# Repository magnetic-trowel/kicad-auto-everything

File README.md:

# kicad-auto-everything
helper systems for LLMing KiCad

## Research

- [`docs/INDEX.md`](docs/INDEX.md): start here. Short digests link to small
  focused topic docs on placement and routing algorithms, LLMs for EDA, KiCad
  integration, layout rules, verification, benchmarks, and licensing.
- [`research_notes/LLM driven PCB placement and routing/`](research_notes/LLM%20driven%20PCB%20placement%20and%20routing/):
  the raw survey notes the docs cite as evidence.

## Design synthesis

- [`synth/`](synth/README.md) (`kaesynth`): an LLM writes a typed circuit description
  (`designs/<slug>/design.py`); `kaesynth build` checks it (ratings vs worst-case net voltage,
  isolation domains, protection, provenance), writes a KiCad 10 schematic and project, proves the
  schematic's netlist matches, and emits placement intent for the placer/router.
- [`designs/`](designs/): worked examples from plain-language briefs.

## License

Code is [GPL-3.0-or-later](LICENSE); documentation and research notes are
CC-BY-4.0, rule packs CC0-1.0, datasets CDLA-Permissive-2.0, and model weights
Apache-2.0. See [`LICENSING.md`](LICENSING.md) for details and
[`CONTRIBUTING.md`](CONTRIBUTING.md) for how to contribute (DCO sign-off).

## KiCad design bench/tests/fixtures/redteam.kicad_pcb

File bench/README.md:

# kaebench

Benchmark harness for automated and LLM-driven KiCad placement and routing. It
fetches real boards from a manifest, turns them into route and place tasks, runs a
method (an "adapter") on each task k times, and scores every attempt by re-opening
the saved board with `kicad-cli` under the board's own rules. Design rationale:
[docs/topics/verification/harness.md](../docs/topics/verification/harness.md).

## Setup (Ubuntu 22.04/24.04)

```bash
git clone https://github.com/magnetic-trowel/kicad-auto-everything
cd kicad-auto-everything
bench/scripts/setup.sh          # KiCad 10 (PPA, no recommends), bench/.venv (and upstream Freerouting 2.5.0, explicit use only)
tools/research/routing/install_freerouting_fork.sh <ref> --pin   # the Freerouting fork, pinned: the control
source bench/.venv/bin/activate
kaebench doctor
```

**Without sudo** the same script still works:
- KiCad runs from the official `kicad/kicad:10.0.7` image, unpacked into `~/.cache/kaebench` (~2.5 GB). It needs no root and no `/dev/fuse`.
- It uses an installed Apptainer or Singularity. Without one, it installs Apptainer 1.5.4 rootless into `~/.cache/kaebench/apptainer` (~160 MB) with Apptainer's own `install-unprivileged.sh`, which unpacks EL8 RPMs. Python stand-ins replace `rpm2cpio` and `cpio` if they are missing.
- The rootless install needs x86_64 and unprivileged user namespaces. Check with `unshare -Ur true && echo ok`. Ubuntu 22.04 allows them by default; 24.04 blocks them unless an admin relaxes `kernel.apparmor_restrict_unprivileged_userns`.
- If `python3-venv` is missing, the venv comes from `uv`.
- Freerouting, the venv and `env.sh` all live in your home directory. Set `KAE_HOME` to put the large files on another disk.
- `source bench/.venv/bin/activate` picks up the KiCad wrapper. Force this route with `--kicad container`.
- The container sees `$HOME`, `/tmp` and the current directory. For a `--workdir` elsewhere, export `APPTAINER_BIND=/that/path`.

Other OSes or setups: point `KAE_KICAD_CLI` / `KAE_KICAD_PYTHON` at KiCad 10. Both accept a command with a wrapper, e.g. `flatpak run --command=kicad-cli org.kicad.KiCad`, or use `KAE_KICAD_WRAP` as a prefix for both. The container set-up points `KAE_KICAD_WRAP` at `kicad-exec`, which shows KiCad only the CPUs a job may use (`KAE_KICAD_THREADS`, else the queue's `KAEQ_CPUS`, else `nproc`; `KAE_KICAD_THREADS=0` turns the cap off): KiCad otherwise starts one thread per CPU on the machine. The Python must be able to `import pcbnew`. Freerouting is the build named by `KAE_FREEROUTING` (a binary or JAR; the JAR needs Java 25), else the one pinned in `$KAE_HOME/kae-freerouting.pin` (the magnetic-trowel fork, the same pin the bridge uses); with neither, runs stop with an error. Nothing picks the newest install. Run `pytest bench/tests` to check the install.

## Usage

```bash
M=bench/manifests/candidates.jsonl
kaebench fetch   -m $M -j 8                 # download boards at pinned commits (verifies sha256)
kaebench prepare -m $M -j 8                 # convert to KiCad 10, qualify, build route/place tasks
kaebench run --adapter reference --kinds route,place --probe freerouting -j 8 --name human
kaebench run --adapter freerouting -k 1 --timeout 900 -j 8 --name fr-fork      # the pinned fork; deterministic: one attempt
kaebench report kae-work/results/human kae-work/results/fr-fork
```

Everything lives under `--workdir` (default `./kae-work`): `cache/` (fetched files),
`tasks/<id>/{reference,route,place,place-fixed}/` and `results/<run>/<adapter>/<kind>/<id>/attempt-N/`.
Runs resume: re-running with the same `--name` skips finished attempts.

Useful filters on `fetch`/`prepare`: `--tiers permissive`, `--tags rf,ddr`, `--only id1,id2`,
`--limit N`. On `run`: `--splits A,B` (A ≤ 31 pads, B ≤ 100, C larger), `--all` to include
boards whose human layout is not clean.

## Suites

`bench/suites/*.txt` are board-id lists for `--only @FILE`:
- `kaebench tasks --write-suite FILE` writes the boards that qualified on your KiCad version.
- `qualified-kicad-10.0.7.txt`: the 112 manifest boards that qualified on KiCad 10.0.7.
- `pcbworld-d3{a,b,c}-test.txt` are PCBWorld's D3 eval splits (99 / 10 / 10).

### Reproducing PCBWorld's routing baseline

PCBWorld's D3 boards are PCBench boards run through PCBWorld's own chain: KiCad 5→9.0.8 conversion, DRC repair, guide generation. Build them with that chain, then import them:

```bash
# in a PCBWorld checkout (https://github.com/LGAI-Research/PCBWorld); builds its KiCad engine
export PCBWORLD_DATA_ROOT=$PWD/var/datasets
bash tools/quickstart/prepare_pcbench.sh --workers 16
# back in this repo
kaebench --workdir kae-d3 prepare-dir --dir $PCBWORLD_DATA_ROOT/pcbench/exacad_sorted \
  --board-glob processed_v9_guide_v3.kicad_pcb --only @bench/suites/pcbworld-d3a-test.txt --kinds route -j 16
KAE_FREEROUTING=<a Freerouting release> kaebench --workdir kae-d3 run --adapter freerouting --passes 10 -k 5 -j 16 --name fr-release-mp10
```

PCBWorld published Freerouting 2.1.0 `-mp 10` at 0.80 (D3-A) and 0.78 (D3-B) clean-pass @5. Our scoring re-saves boards with KiCad 10 and uses each board's own severities. Expect close but not identical numbers; report both.

## Adapters

| Adapter | What it does |
|---|---|
| `reference` | The human layout: original copper (route) or original placement (place) |
| `noop` | Returns the task input unchanged (lower bound) |
| `freerouting` | Specctra DSN → the pinned Freerouting (the fork, our control; `-mt 1`, analytics off, per-attempt pass schedule, neck-down off, board edge/hole clearances passed, DSN widths clamped to the board minimum) → SES with placement block stripped → import |
| `freerouting-stock` | Same round trip with Freerouting's default settings; for explicit, deliberate use only (stock 2.5.0 is no longer a control) |
| any name + `--command` | External tool; template placeholders `{input} {output} {workdir} {kind} {attempt} {timeout}` |

Example external router: `kaebench run --adapter myrouter --command "python my_router.py {input} {output}"`.
The tool reads `{input}` (a `.kicad_pcb` with its project files beside it) and writes `{output}`.

**Sandbox.** `--command` methods run under bubblewrap (`bwrap`):
- no network;
- a private `/tmp` and `/var/tmp`;
- a home directory that shows only the kaebench tool cache (`KAE_HOME`), the current directory and any `--sandbox-ro PATH`;
- the workdir's tasks and results hidden, plus anything in `KAE_SANDBOX_HIDE` (colon-separated);
- only the attempt's own work directory writable.

A method can't read the human layout it is scored against, download it, or touch other attempts. On timeout the whole sandbox is killed. `--sandbox-net` allows network access, for LLM methods. `--no-sandbox` turns the sandbox off; the report then marks those attempts as unsandboxed.

## Scoring

- **Rebuilt board, reference rules, fresh process.** The scorer never judges the file a method wrote. It rebuilds the board from the task input plus only the changes the task allows:
  - route: the tracks, arcs and vias, copied as KiCad's own re-save of them, plus (score v10) the copper zones the method adds, unfilled, and each pad's own zone connection (`zone_connect`);
  - place: each unlocked footprint's position, rotation and side.

  The rebuilt board gets the reference `.kicad_pro`/`.kicad_dru`, zones are refilled, and `kicad-cli pcb drc` runs. Edits to rules, outline, keepouts, the task's zones, other pad properties, layers or nets can't change a score. Rules files a method writes are never read: the output is opened next to the task's own project files.
  - Teardrops, groups and tuning patterns are part of the routing. They are stripped from task inputs and are not transplanted or scored.
- **Integrity (`valid`).** Anything else the method changed is still detected, by comparing KiCad re-saves of output and input with the allowed changes normalized away (`foreign` lists them). Such a result is invalid.
  - Route results must keep placement, pad nets and every other board object, and route only on the board's copper layers and nets.
  - **Added zones** (route, joint and joint-fixed tasks, score v10). A method may pour copper. Each added zone must be a copper zone (no rule area or keepout) on the board's enabled copper layers, on a net the task has (no new nets, no net-less zones), inside the board's outer outline (10 µm slack for arcs), clear of rule areas that forbid pours on its layers, at a priority different from every zone it overlaps on a shared layer (KiCad 10.0.7's filler deadlocks on overlapping zones of different nets tied on priority and uuid), and with a unique uuid. Violations make the result invalid (`integrity.zones`, reasons in `zone_problems`). The task's own zones must stay exactly as given. These checks look at zone outlines; DRC checks the refilled copper (clearances, edge clearance, `items_not_allowed` in keepouts). Fills a method writes are ignored: DRC refills every zone, and the uncapped unconnected count fills them too, at start and end alike. Give new zones explicit pad-connection settings (clearance, thermal gap, spoke width) rather than relying on board defaults. No count or area cap; refilling many zones counts against `KAE_DRC_TIMEOUT` like anything else. In joint tasks the placement half ignores added zones and pads' zone connection (placement legality is judged on the placement alone); the routing half transplants and checks them onto that placement as in a route task.
  - Place results must keep pad nets and every non-pose property, leave anchored footprints where they are (locked ones, and ones carrying Edge.Cuts, which are part of the board outline), and not add or remove footprints or copper.
- **Copy check.** `copy` reports how much of the output reproduces the human layout exactly: tracks to 1 µm, or poses to 1 µm and 0.01°; and `copy.zones`, added zones whose outline overlaps a human zone on the same net and a shared layer with IoU ≥ 0.8. `suspect_copy` flags at least 20 tracks and 60% matching, at least 5 parts and 50%, or any copied zone. It is report-only until calibrated on real methods. The sandbox is the enforcement.
- **Route metrics.**
  - `clean`: valid, 0 unconnected, 0 error-level DRC violations. Severities come from the board's own project; library-environment checks are excluded.
  - `completion`: share of start-of-task unconnected items now routed.
  - `wl_ratio`: track length relative to the human layout.
  - `via_delta`: via count minus the human layout's.
- **Place metrics.**
  - `legal`: valid, no courtyard, clearance, edge-clearance, hole or keepout errors, and no footprint with more pad centres outside the board outline than the same footprint has in the human placement. Edge connectors may overhang as far as the designer's do.
  - `hpwl_ratio` relative to the human placement.
  - With `--probe freerouting`, the rebuilt placement is routed by a fixed router and scored like a route result, Cypress-style. An external router can be the probe: `--probe NAME --probe-command TEMPLATE` (or `probe=NAME,probe_command=TEMPLATE` in an `--arm`, without commas), run sandboxed as a route method.
- **Joint metrics** (`--kinds joint`: place and route in one output, from the place task's input).
  - The output's footprint poses are rebuilt into the place input. Placement integrity and `legal` are judged on that placement alone.
  - Its tracks and vias are then rebuilt onto that placement and scored like a route result.
  - Valid only if both parts are; `clean` also requires `legal`.
  - Baselines: `reference` (the human layout) and `human-freerouting` (Freerouting on the human placement).
- **Place-fixed tasks** (`--kinds place-fixed`, and `joint-fixed` for place and route from its input). A place task frees every unlocked footprint, the connectors and mounting holes too, so a placer can beat the human on wire length with a board that no longer fits its enclosure or cables. Place-fixed keeps the board's mechanical interface at the human pose, locked in the input, so it is scored exactly like a locked footprint (`locked_moved`); everything else is placed. Scoring and baselines are those of `place` and `joint`.
  - Fixed: connectors (USB, pin headers and sockets, JST/Molex/FPC/FFC, terminal blocks, barrel and audio jacks, RF, SD/SIM and card-edge slots, wire pads); mounting (screw holes, standoffs, fiducials, all-NPTH footprints); user-facing parts (switches, keyboard key switches such as Cherry MX, Kailh/Choc and Gateron, buttons, panel pots and encoders, displays, through-hole, light-pipe and LED-bar indicators, buzzers and speakers).
  - Free (the user's choices on borderline parts): programming and debug headers (JTAG, SWD, ISP/ICSP, PDI/UPDI, Tag-Connect, debug or prog in the name, value, description or reference, or a small header whose signal nets are one such interface), SMD LEDs, test points, jumpers and solder bridges (also pin headers with a jumper value), batteries and battery holders, trimmers, IC sockets; also net ties, heatsinks and plug-in modules. UART and display headers stay fixed.
  - The rules follow the placement research classifier (`kae.place.fixed`); on the 112 qualified boards the two fix the same parts on 99 boards.
  - Rules, first match wins (`kicad_scripts/mech_rules.py` documents each, `rules_version` is recorded): exclusions; KiCad library (`Connector*`, `TerminalBlock*`, `MountingHole*`, `Fiducial*`, `Button_Switch*`, `Potentiometer*`, `Rotary_Encoder*`, `Display*`, `Buzzer_Beeper*`, `LED_THT`, connector makers); all pads NPTH; a THT LED name; a passive/diode/IC library, package name or reference (R, C, D, Q, ...) stops the rest; footprint-name patterns; KiCad symbol names as values (`Conn_01x04`, `SW_Push`); reference prefixes (J, P, H, MH, FID, SW, RV, ...) when the footprint fits. A connector that is a programming or debug header is then freed.
  - The task record lists every fixed part with its class and rule (`tasks["place-fixed"].fixed_mech`) and `movable`. `prepare --fixed-overrides FILE` takes `{"<board id>": {"fix": [refs], "free": [refs]}}` and records what it applied. Designer-locked parts and parts carrying Edge.Cuts stay anchored either way.
  - The human placement must also pass the place-fixed round trip. A board that fails it keeps its other tasks; runs skip only its place-fixed and joint-fixed tasks.
- **Degenerate place tasks.** Each place task records `movable`, the number of footprints a placer may move. A board whose parts are nearly all locked is trivially legal. `run --min-movable N` skips place, joint, place-fixed and joint-fixed tasks with fewer than N movable footprints (default 0: none are skipped).
- **Best-of-k** picks the attempt by clean, then completion, errors, track length (PCBWorld's best-potential @k). The report shows `cp1` (attempt 0) and `cpk`.
- **Rescoring.** After a scoring fix, `kaebench rescore RUN_DIR -j N` scores a run's saved outputs (and saved probe routes) again with the current scorer, without re-running the method. Each attempt records the version it was rescored from.
- **Versions.** Every attempt records `score_version` (now 10; v10 lets route and joint methods add zones and set pads' zone connection, and scores outputs without either exactly as v9). Tasks need task spec 5: locked footprints and footprints carrying Edge.Cuts stay in place, teardrops are stripped, repeated footprint uuids are made unique, and the human layout must pass the round trip. Place-fixed and joint-fixed need task spec 8 (classifier rules 4). From task spec 11 every task is limited to the copper layers the board uses (`kicad_scripts/layer_plan.py`); tasks of older specs must be prepared again. Re-run `prepare --force` on older task folders.
- **Red-team tests.** `bench/tests/test_redteam.py` runs cheating methods (move parts, delete a keepout, grow the outline, add a layer, shrink pads, swap nets, ship own rules, read or overwrite the reference, use the network) and requires each to be invalid, blocked or ineffective. Add a case for every new cheat found.

## Manifests

`bench/manifests/*.jsonl`, one board per line: `id`, `repo`, `commit` (40-hex),
`pcb_path`, `license` (required), plus `pcb_sha256`, `license_tier`, stats and
`tags`. Boards are never redistributed; only manifests are committed
(CDLA-Permissive-2.0).

- `candidates.jsonl`: the 297-board benchmark set.
- `wide.jsonl` (13,475) and `wide-noncommercial.jsonl` (843): the second sourcing pass,
  see [wide-board-corpus](../docs/topics/data/wide-board-corpus.md). Filter with
  `--tiers` and `--tags` (e.g. `--tags drc-clean`); `host-robots-restricted` marks rows on
  hosts whose robots.txt disallows raw/git paths.
- `pcb_path` may be an Eagle/Allegro `.brd`, Altium `.PcbDoc`, PADS `.asc` or CADSTAR `.cpa`;
  `fetch` converts it with `kicad-cli pcb import` and `pcb_sha256` stays the upstream hash.
- Rows with `archive_sha256` and `commit: null` are downloads (zip, tar or a single file),
  pinned by that hash.

## Known limitations

- KiCad 10 SES import deletes unlocked copper and applies placement. The adapter strips the SES placement block, and route tasks start without copper.
- Freerouting necks tracks down below the board's minimum width near fine-pitch pads and shrinks some to 75% to meet edge clearance; the `freerouting` adapter disables neck-down, but edge-driven shrinking remains (KiCad flags it as `track_width`).
- Freerouting has no seed flag, so best-of-k varies the pass count (`-mp` 10, 20, 30, ...).
- `inside` uses pad centres against the board outline. Courtyard-vs-edge overhang is not checked.

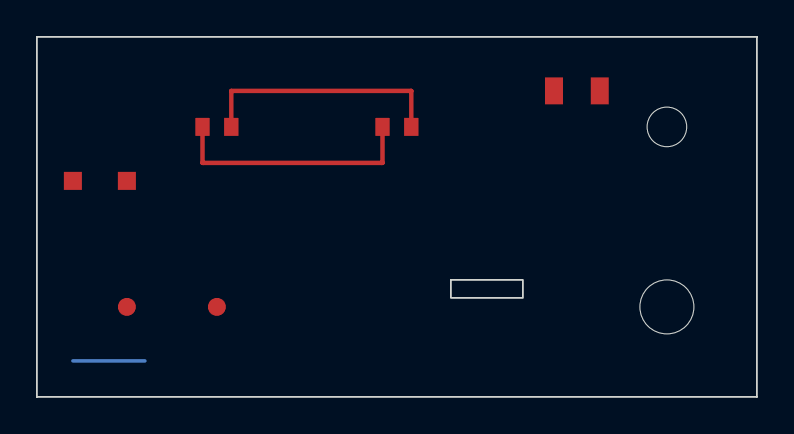
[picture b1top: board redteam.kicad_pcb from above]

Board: 2 copper layers, 40.0 x 20.0 mm, 9 parts (0 on the bottom side), 2 nets.

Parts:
H1: MH
H2: MountingHole; MountingHole_2.2mm_M2
J1: Conn_01x02; PinHeader_1x02_P2.54mm_Vertical
R1, R2: R
SL1: SLOT
SW1: SW_Push; SW_Push_Test
TP1, TP2: TP

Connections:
N1: R1.1, R2.1
N2: R1.2, R2.2

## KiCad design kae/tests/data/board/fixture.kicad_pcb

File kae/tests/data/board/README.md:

# Test fixture board

`fixture.kicad_pcb` (with `.kicad_pro`, `.kicad_dru` and `fixture.pcbnew.json`, pcbnew's extraction of the same board) is a synthetic 4-layer KiCad 10 board made by this project for the loader tests (commit 64a6858, 2026-10-22). Its footprints come from a made-up `kae_test:` library and its rules are invented; it is not derived from any third-party design. Licence: GPL-3.0-or-later, as the rest of the repository (`REUSE.toml`).

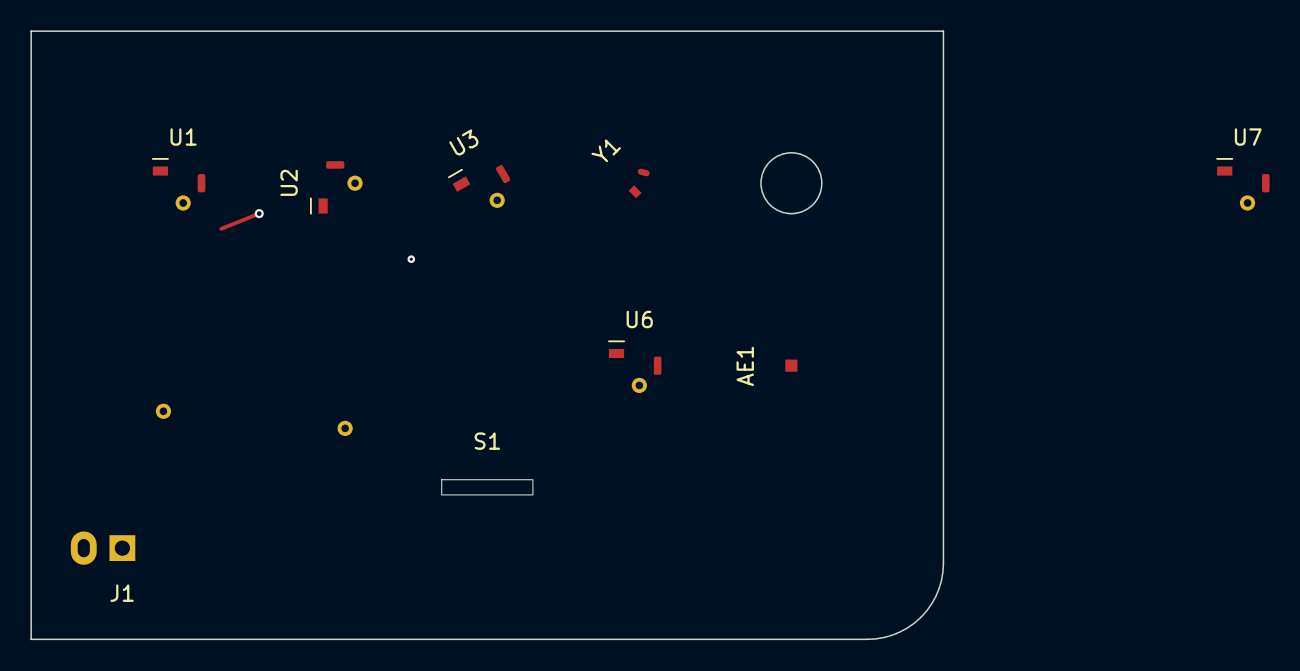
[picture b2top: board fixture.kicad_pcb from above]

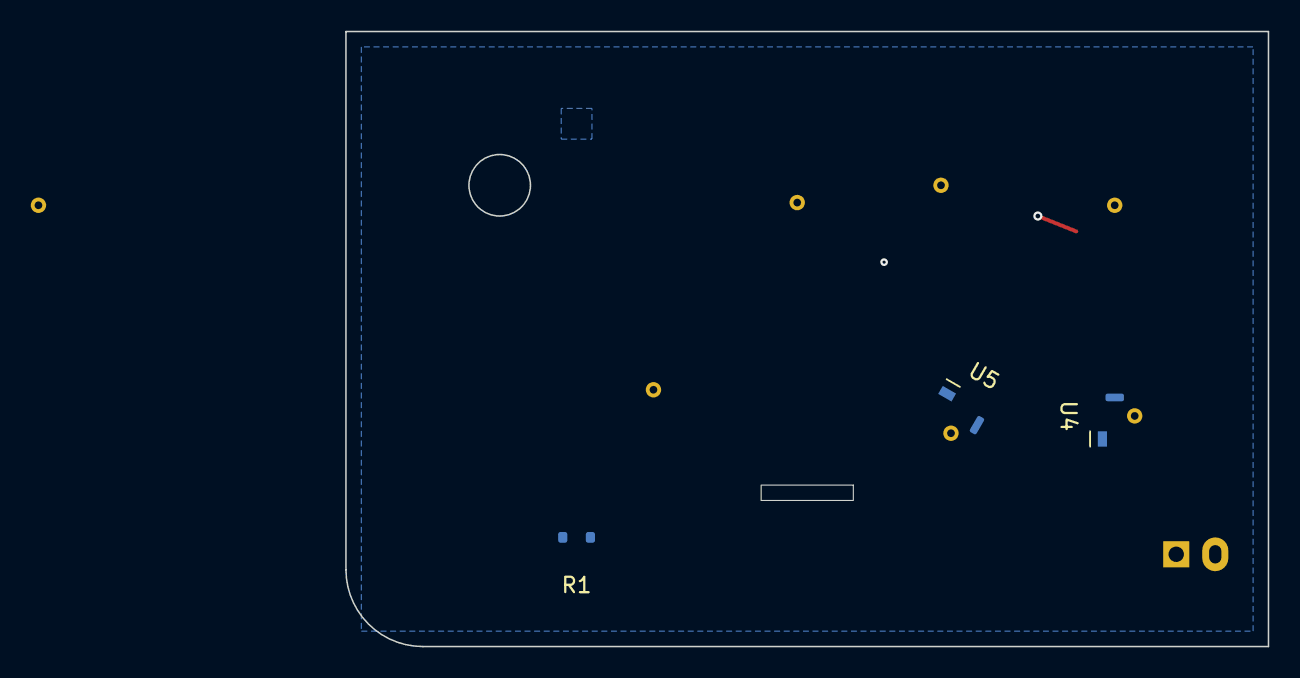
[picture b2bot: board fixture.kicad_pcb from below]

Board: 4 copper layers, 60.0 x 40.0 mm, 12 parts (3 on the bottom side), 5 nets.

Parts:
AE1: ANT
J1: CONN; THT2
R1: 10k; NOCRT
S1: SLOT
U1, U2, U3, U4, U5, U6, U7: ASYM; ASYM3
Y1: XTAL; ROUND

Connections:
GND: J1.2 (GND), R1.2, U1.2 (GND), U2.2 (GND), U3.2 (GND), U4.2 (GND), U5.2 (GND), U6.2 (GND), U7.2 (GND), Y1.2
SIG1: AE1.1, U1.1 (IN), U4.1 (IN), U7.1 (IN)
SIG2: U2.1 (IN), U5.1 (IN), Y1.1
SIG3: R1.1, U3.1 (IN), U6.1 (IN)
VCC: J1.1 (VCC), U1.3 (VDD), U3.3 (VDD), U4.3 (VDD), U5.3 (VDD), U6.3 (VDD), U7.3 (VDD)
